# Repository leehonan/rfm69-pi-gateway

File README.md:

# Meterman Gateway (RFM69-to-Pi Gateway)

This repo contains PCB designs and firmware for a 'meter gateway' that communicates with one or more 'meter nodes' over packet radio.  It acts as a radio gateway between these and logic running on a local server.  Hardware consists of a ATMEGA 328P (with RFM69 radio), and a daughterboard to mate to a Raspberry Pi for Serial UART TX/RX and power (AKA a Pi Hat).  The PCB design could be used for a general-purpose RFM69-Pi Gateway, hacking the firmware code as needed.

(Note that as above a proper case is TBC)

This Gateway is part of a basic electricity monitoring system described at http://leehonan.com/meterman.  The 'MeterMan' system consists of:

* One or more [MeterNodes](https://github.com/leehonan/meterman-node), transmitting energy consumption at set intervals using sub-GHz packet radio (RFM69 @ 434/868/915MHz).

* The Gateway, being a Raspberry Pi 'Hat' that bridges the RFM69 network to a Raspberry Pi's UART Serial interface.

* A [Server](https://github.com/leehonan/meterman-server) that runs on the Pi, maintains energy consumption data, and provides access to this and other operational data through an API, a file journal, and a realtime socket API (socket API is TBD).

## This Repo

This (Gateway) repo consists of:

* The Gateway PCB design (authored in KiCad).  This mounts onto a Raspberry Pi, with ~12mm x 2.5mm spacers being recommended.

* 3D shape files (.STL) for the gateway housing (WIP).

* Source code for the Gateway firmware (AVR C with Arduino extensions).  

All contents are licenced according to the MIT licence.

## Gateway Overview
The Gateway is essentially a bridge between nodes on a RFM69 network and a local application connected to the Pi's UART serial port.  As the Gateway has been designed to support MeterNodes, much of the context for it is best understood by consulting the more comprehensive [MeterNode's ReadMe](https://github.com/leehonan/meterman-node/blob/master/readme.md) - it is not repeated here (DRY).

The Gateway itself comprises:
* A DC power sub-circuit, switchable using a jumper between 5V from the Raspberry Pi and FTDI (or off if no FTDI connection).  Uses a MCP1700 regulator to supply 3.3VDC.  

* An ATMega 328P MCU sub-circuit, along the lines of common 'minimal low-power Arduino' circuits.  FTDI Header for programming and control.

* A radio sub-circuit with an RFM69HW module.  The design uses an RP-SMA connector, but the PCB also supports uFL or a wire antenna.

The gateway does not have a 'real' RTC.  A timer-based clock is implemented in firmware, although this relies on regular synchronisation with its NTP-synced Pi (e.g. every 15m) to be accurate.

## Operation

 The Gateway:
* Polls for radio messages from nodes, responding to these as needed.  These may indicate events or status changes, which are passed through to the connected application (such as a meter update event).

* Keeps a register of meter nodes, maintaining state information and notifying the connected application when they appear to go offline.

* Polls for serial messages from the connected application, responding to these as needed.  Some of these will cause a particular instruction to be sent to a MeterNode(s) when they are available (e.g. to change their meter value).

* Sends messages to the connected application, such as a request from the Gateway to sync its clock.

The gateway runs continuously and does not sleep.  Its availability for radio messaging can therefore be depended upon by MeterNodes - hence all communication between MeterNodes and their Gateway is initiated by the MeterNodes.

### Gateway Hardware Interface
The MeterNode PCB has the following switches, buttons, headers, and adjustable components.  These are shown below.

* A group of 3 jumpers that toggle between the Pi and FTDI for TX from the MCU, RX by the MCU, and 5VDC In.  If the jumper is in the FTDI position but FTDI is not connected the device will be off.  Conversely if the switch is in the Pi position but a FTDI adapter is connected, power will be drawn from the Pi (with other FTDI functions working as normal).

* A 'Pi Off' button that shuts the Pi down (using the accompanying pi-gw-reboot script).

* A 'Pi Res' button that reboots the Pi (using the accompanying pi-gw-reboot script).

* A MCU Reset button that reboots the MCU.

* A MCU Aux button that can be programmed as needed (currently blinks LED).

* A jumper to allow the Pi to reboot the MCU (used when programming the MCU, safe to leave closed).

* An FTDI header for use with a USB-FTDI adapter.  This is used to upload firmware and also to interact with the MCU directly over a serial connection (viewing events and using the MeterNode's command protocol to view information and change settings).  Firmware can be uploaded using avrdude directly, or via an IDE (such as platform.io).  The use of the FTDI header is usually unnecessary with a Pi connected as all commands/operations can be performed from the Pi using its GPIO pins (assuming the enclosed scripts are installed).

* A breakout header that is used for setup and diagnosis, typically with a multimeter.  These can also be used for hacking together custom solutions.  The positions are described below and pictured above:

| Position | Description |
| :--- |:---|
| A0 - D8 | Access to unused analogue (A0 - A2) and digital (D3-D8) pins on the MCU. |
| GND | DC Ground. |
| 3V3   | 3.3VDC from regulator.  |
| 5V  | ~5VDC from Pi.  |

### Shutdown and Reboot
The Restart/Reboot and Shutdown buttons are connected to GPIO P23 and P24 (board numbering).  They perform a soft reboot or shutdown, equivalent to a `reboot` or `shutdown -h now`.

The enclosed pishutdown.py script needs to be installed for these to function, and to be set to start at boot.

A service script is enclosed in `/src`.  This can be installed as follows:
```
cp pishutdown.service /lib/systemd/system
chmod 644 /lib/systemd/system/pishutdown.service
systemctl daemon-reload
systemctl enable pishutdown.service
systemctl start pishutdown.service
```

Otherwise simple way to start on boot is to use cron, e.g.:
```
@reboot /usr/local/bin/python3.6 /home/pi/pishutdown.py
```

### Uploading Firmware
Firmware is uploaded using avrdude (alternately through an IDE such as atom/platform.io, the Arduino IDE may work too).  For an FTDI adapter with Id A403JXEV on OSX or Linux the command will be something like:

```
sudo avrdude -c arduino -p atmega328p -P /dev/cu.usbserial-A403JXEV -b 115200 -U flash:w:/home/tmp/firmware.hex
```
In practice for the gateway, it is easiest to upload firmware using scp and then to flash over the GPIO header using avrdude.  E.g.
```
scp /Users/lee/meter_gateway/firmware.hex meterman@meterbox:

sudo avrdude -c arduino -p atmega328p -P /dev/serial0 -b 115200 -U flash:w:/home/meterman/firmware.hex
```

For this to work, avrdude needs to be patched to work around the absence of a DTR pin on the RPi.  The files are enclosed in this repo's `/src` directory, and can be installed using the following commands (as sudo), or by executing the meterman setup script (from the meterman repo) on the pi.
```
cp autoreset /usr/bin
cp avrdude-autoreset /usr/bin
chmod +x /usr/bin/autoreset
chmod +x /usr/bin/avrdude-autoreset
mv /usr/bin/avrdude /usr/bin/avrdude-original
ln -s /usr/bin/avrdude-autoreset /usr/bin/avrdude
```

The flash process will only work if there are no active serial sessions on the port chosen.  Flashing fails occasionally for no clear reason, but will work when retried.

### Serial Communication & Console
A serial connection can be made using a baud of 115200bps, 8N1 (8 data bits, no parity bit, 1 stop bit).  

On the RPi minicom can be used (as can screen etc) to open a terminal:
```
sudo minicom -b 115200 -o -D /dev/serial0
```
Ensure that hardware flow control is off.

The following commands are available through the serial console (case-insensitive):

| Command | Description |
| :--- |:---|
| help | Prints a list of commands. |
| z  | Toggles sleep on and off. |
| dumpg | Prints (dumps) Gateway config and status to the console.  |
| dumpn | Prints (dumps) node status to the console (with dumpn=[node_id] to specify a node).  |
| rcfg | Reset Config.  Resets configuration values stored in EEPROM to defaults and re-applies these.  |
| time | Prints current time from RTC. Set using time=[seconds since UNIX epoch, UTC] |
| logl | Prints log level - ERROR, WARN, INFO, DEBUG.  Set with logl=[log level]|
| ekey | Prints encryption key (16 byte AES) used by network participants for radio comms.  Set with ekey=[encryption key], e.g. ekey=CHANGE_THIS_ASAP|
| neti | Prints Gateway's Network Id comprised of octets akin to an IP address but with an extra subnet (as the 4 octets define a subnet, with node addressing within this).  Set with neti=[network_id].  At least two octets need to be non-zero so 0.0.1.1 is the 'lowest' usable network subnet.  E.g. neti=0.0.1.1|
| gwid | Prints the 'node id' for the gateway.  This should be 1 by convention, but can be any unallocated address from 1 to 253. Set with gwid=[gateway Id]|
| txpw | Print/set transmission power (set with TXPW=[tx power in dBi]).  For RFM69W range is -18 to +13, for RFM69HW is -14 to +20. Higher values will use more power. |
| enta | Sets meter nodes to be in alignment mode (set on with ENTA=1, off with ENTA=0). When on, a change to a MeterNode's RTC will cause it to wait until mm:00 before opening a new entry.  |

### Pi-to-Gateway Serial Message Protocol
The serial port is also used for communication between the Pi and the Gateway.  In normal operation the user-driven command protocol should be unnecessary, as all key functions are exposed through this interface (intended to be used by the Meterman server application).

Messages are distinguished from user commands and user feedback/logging by a prefix:
* for a message from the Gateway to the Pi Server ```G>S:<message>```

* for a message from the Pi Server to the Gateway ```S>G:<message>```

| Message | From | To | Description|
| :--- |:---| :--- |:---|
| Get Time  | gateway | server | Request for server to return time, allowing gateway to sync its internal clock. <br>Format: `GTIME`<br>E.g.: `GTIME` |
| Set Time | server | gateway | Instruction to gateway to set its clock to the time provided (seconds since UNIX epoch) <br>Format: `STIME;<new_epoch_time_utc>`<br>E.g.: `STIME;1502795790`|
| Set Time Ack  | gateway | server | Acknowledges receipt of valid instruction.<br>Format: `STIME_ACK`<br>E.g.: `STIME_ACK` |
| Set Time Nack  | gateway | server | Negative acknowledgement of set time instruction, likely malformed. <br>Format: `STIME_NACK`<br>E.g.: `STIME_NACK` |
| Get Gateway Snapshot | server | gateway | Request for gateway status dump. <br>Format: `GGWSNAP`<br>E.g.: `GGWSNAP` |
| Gateway Snapshot | gateway | server | Dump of Gateway Status <br>Format: `GWSNAP;<gateway_id>,<when_booted>,<free_ram>,<time>,<log_level>,<encrypt_key>,<network_id>,<tx_power>`<br>E.g.: `GWSNAP;1,1496842913428,577,1496842913428,DEBUG,PLEASE_CHANGE_ME,0.0.1.1,13` |
| Get Node Snapshot | server | gateway | Requests a dump of a node's state from the Gateway.  All nodes observed by the gateway since boot will be returned (there is no registration process - any with correct subnet and key are assumed to be valid members). <br>Format: `GNOSNAP;<node_id>   - returns all nodes if no node_id or node_id=254`<br>E.g.: `GNOSNAP;2` |
| Node Snapshot | gateway | server | A snapshot of one or more nodes, delimited by ';'. <br>Format: `NOSNAP;[1..n of [<node_id>,<batt_voltage>,<up_time>,<sleep_time>,<free_ram>,<when_last_seen>,<last_clock_drift>,<meter_interval>,<meter_impulses_per_kwh>,<last_meter_entry_finish>,<last_meter_value>,<puck_led_rate>,<puck_led_time>,<last_rssi_at_gateway>]]`<br>E.g.: `NOSNAP;2,4500,15000,20000,600,1496842913428,500,5,1496842913428,3050,1,100,1000,-70` |
| Get Node Snapshot Nack | gateway | server | Negative acknowledgement of request, likely malformed. <br>Format: `GNOSNAP_NACK;<node_id>`<br>E.g.: `GNOSNAP_NACK;2` |
| Meter Update - with Current | gateway | server | Pass-through of message from meterman node, with envelope. <br>Format: `MUPC;<node_id>,<MUPC radio message>`<br>E.g.: `MUPC;2,MUPC,1496842913428,18829393;15,1,10.2;15,5,10.7;` |
| Meter Update - without Current | gateway | server | Pass-through of message from meterman node, with envelope. <br>Format: `MUP_;<node_id>,<MUP_ radio message>`<br>E.g.: `MUP_;2,MUP_,1496842913428,18829393;15,1;15,5;15,2;16,3;` |
| Meter Rebase | gateway | server | Pass-through of message from meterman node, with envelope. <br>Format: `MREB;<node_id>,<MREB radio message>`<br>E.g.: `MREB;2,MREB,1496842913428,18829393` |
| General Message (Broadcast) | gateway | server | Pass-through of message from meterman node, with envelope. <br>Format: `GMSG;<node_id>,<GMSG radio message>`<br>E.g.: `GMSG;2,GMSG,message` |
| Set Meter Value | server | gateway | Requests a reset of a node's meter value to the watt-hour value specified <br>Format: `SMVAL;<node_id>,<new_meter_value>`<br>E.g.: `SMVAL;2,10` |
| Set Meter Value Ack | gateway | server | Acknowledges receipt of valid instruction. <br>Format: `SMVAL_ACK;<node_id>`<br>E.g.: `SMVAL_ACK;2` |
| Set Meter Value Nack | gateway | server | Negative acknowledgement of request, likely malformed. <br>Format: `SMVAL_NACK;<node_id>`<br>E.g.: `SMVAL_NACK;2` |
| Set Puck LED | server | gateway | Requests a change of a node's puck LED rate and time. <br>Format: `SPLED;<node_id>,<new_puck_led_rate>,<new_puck_led_time>`<br>E.g.: `SPLED;2,1,100` |
| Set Puck LED Ack | gateway | server | Acknowledges receipt of valid instruction. <br>Format: `SPLED_ACK;<node_id>`<br>E.g.: `SPLED_ACK;2` |
| Set Puck LED Nack | gateway | server | Negative acknowledgement of request, likely malformed. <br>Format: `SPLED_NACK;<node_id>`<br>E.g.: `SPLED_NACK;2` |
| Set Meter Interval | server | gateway | Requests a change of a node's metering interval to the value specified.  The interval is the period in seconds at which meter entries are created i.e. (resolution). <br>Format: `SMINT;<node_id>,<new_meter_interval>`<br>E.g.: `SMINT;2,10` |
| Set Meter Interval Ack | gateway | server | Acknowledges receipt of valid instruction. <br>Format: `SMINT_ACK;<node_id>`<br>E.g.: `SMINT_ACK;2` |
| Set Meter Interval Nack | gateway | server | Negative acknowledgement of request, likely malformed. <br>Format: `SMINT_NACK;<node_id>`<br>E.g.: `SMINT_NACK;2` |
| Set GITR | server | gateway | Sends request to gateway to set node's gateway instruction polling rate to more aggressive value for a temporary period <br>Format: `SGITR;<node_id>,<tmp_poll_rate>,<tmp_poll_period>`<br>E.g.: `SGITR;2,30,300` |
| Set GITR Ack | gateway | server | Acknowledges receipt of valid instruction. <br>Format: `SGITR_ACK;<node_id>`<br>E.g.: `SGITR_ACK;2` |
| Set GITR Nack | gateway | server | Negative acknowledgement of request, likely malformed. <br>Format: `SGITR_NACK;<node_id>`<br>E.g.: `SGITR_NACK;2` |
| Node Dark Alert | gateway | server | One-time alert on node going from seen to 'missing' after configured period <br>Format: `NDARK;<node_id>,<last_seen>`<br>E.g.: `NDARK;2,1496842913428` |

### Radio Protocol
See the <a href="https://github.com/leehonan/meterman-node/blob/master/readme.md#radio-protocol">MeterNode Radio Protocol documentation</a>.

## Implementation - Gateway Firmware
For simplicity, the firmware is implemented as a single C++ program (no header file), although it will need supporting libraries to compile.  There is some redundancy versus the companion meternode firmware - the common components may be moved to a library.  Some Arduino library features are used.

The firmware requires a 328P that has been flashed with Optiboot.  It uses about 90% available program flash memory.

Depending on configuration, about 500 bytes RAM will remain free at runtime (on average, of 2K).  

There are a number of configuration settings at the beginning of the source code.  Particular attention should be paid to the 'Main Config Parameters'.

Note that a version is set in the firmware, and broadcast on boot.

The code is fairly well-documented so isn't covered further here.

## Implementation - PCBs & Cases

The Gateway PCB measures 65x56mm, being a standard Raspberry Pi Hat size.

A case for the Pi and Gateway is TBD, currently I use a regular Pi case and tape the antenna to it.

Of course, the MeterNode and Gateway antennae should be in the same orientation to maximise signal strength.

### Gateway Schematic & PCB

The PCB design minimises the use of SMT components, and uses through-hole instead.  It is 'hobbyist-friendly' with the only SMT component being the easily-solderable RFM69 and the slightly fiddly uFL connector.  

Highlights:

* The MCP1700 regulator (3.3V) was chosen for consistency with the MeterNode.

* Unlike the MeterNode, I usually use a uFL connector here.  Of course a RP-SMA connector, or even a wire of the appropriate length can be used instead.

* Any RFM69W or RFM69HW module will work.  I use the RFM69HW here (as opposed to the MeterNode's RFM69W) because it is cheaper and there is no need to minimise power consumption on the gateway.

* Of course, the Pi's 2x20 GPIO header needs to face downward (towards the Pi).  Be mindful of this when assembling.

### Parts List

Approx total is USD$11 (not including labour!).  That assumes you purchase common parts in quantity from Chinese suppliers (e.g. resistors, capacitors).  Otherwise cost will be radically higher.  

| Part | Qty | Approx <br>Item Cost<br>(USD) | Comments |
|:---| :--- |:---|:---|
| PCB | 1 | $0.50 | E.g. 10 for $5 at PCBWay |
| Case | 1 | $0.50 | 3D-printed, PLA |
| LED | 1 | $0.02 | Super-bright 5mm, 20mA |
| RP-SMA 3dbi Antenna | 1 | $2.90 | I use higher quality ones via RocketScream, cheaper options available. |
| uFL Connector w/ pigtail | 1 | $1.00 |  |
| MCP1700 Regulator | 1 | $0.50 | 3.3V, TO-92 |
| MCU - ATMEGA 328P | 1 | $1.80 | DIP-28, with holder |
| 16MHz Crystal | 1 | $0.20 | |
| RFM69HW Module | 1 | $2.50 | SMD |
| Resistor - 1 KOhm | 1 | $0.01 | 0.25W |
| Resistor - 10 KOhm | 6 | $0.01 | 0.25W |
| Capacitor - 22 pF | 2 | $0.01 | Ceramic disc |
| Capacitor - 100 nF | 4 | $0.01 | Monolithic, Ceramic |
| Capacitor - 1 uF | 1 | $0.02 | Electrolytic |
| Capacitor - 1 uF | 2 | $0.01 | Monolithic, Ceramic |
| Capacitor - 10 uF | 1 | $0.02 | Electrolytic, 4x7mm |
| Diode - 1N4148 | 1 | $0.01 |  |
| 6x6mm pushbutton | 4 | $0.02 |  |
| Pin Header | 1 | $0.02 | 6P, 2.54mm pitch |
| Pin Header | 3 | $0.01 | 3P, 2.54mm pitch |
| Pin Header | 1 | $0.01 | 2P, 2.54mm pitch |
| Jumper Cap | 4 | $0.01 | 2P, 2.54mm pitch |
| Pi GPIO Header | 1 | $0.10 | 2x20, 40P, 2.54mm pitch |

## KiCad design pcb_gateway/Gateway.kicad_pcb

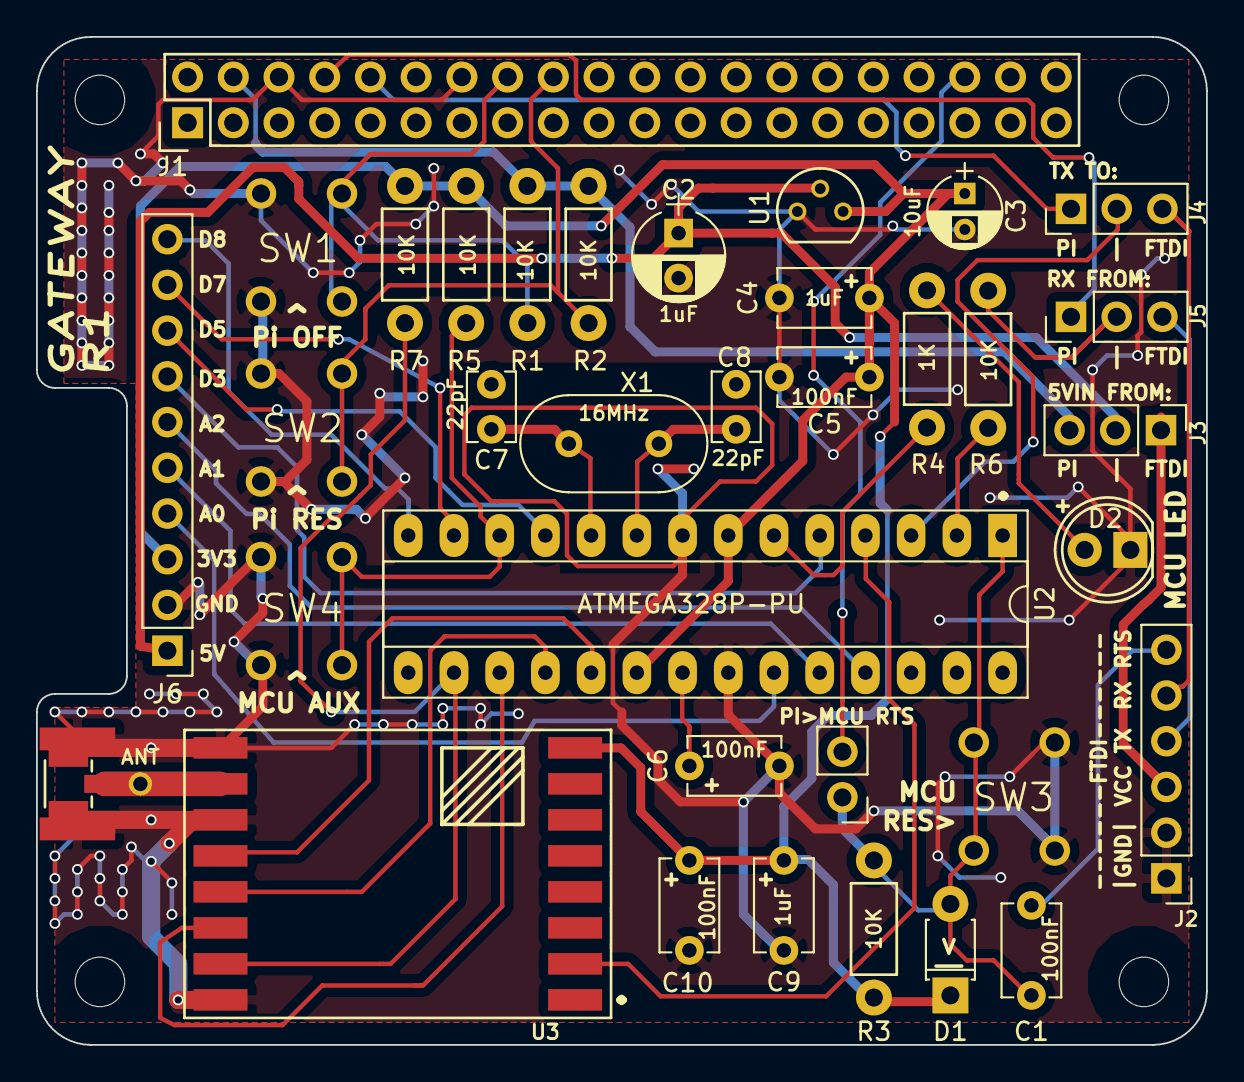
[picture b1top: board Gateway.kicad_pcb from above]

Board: 2 copper layers, 65.0 x 56.0 mm, 37 parts (0 on the bottom side), 36 nets.

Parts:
C1, C5, C6, C10: 100nF; C_Disc_D5.1mm_W3.2mm_P5.00mm
C2: 1uF; CP_Radial_D5.0mm_P2.50mm
C3: 10uF; CP_Radial_D4.0mm_P2.00mm
C4, C9: 1uF; C_Disc_D5.1mm_W3.2mm_P5.00mm
C7, C8: 22pF; C_Disc_D3.8mm_W2.6mm_P2.50mm
D1: 1N4148; D_T-1_P5.08mm_Horizontal
D2: LED; LED-5MM
J1: RPi_GPIO; Pin_Header_Straight_2x20
J2: CONN_FTDI; Pin_Header_Straight_1x06_Pitch2.54mm
J3: JPR_VIN; Pin_Header_Straight_1x03_Pitch2.54mm
J4: JPR_MCU_TX; Pin_Header_Straight_1x03_Pitch2.54mm
J5: JPR_MCU_RX; Pin_Header_Straight_1x03_Pitch2.54mm
J6: CONN_BREAKOUT; Pin_Header_Straight_1x10_Pitch2.54mm
J7: ANT-UFL; U.FL-R-SMT
J8: ANT-SMA; RF-SMA-EDGE
J9: ANT; Pin_Header_Straight_1x01
J10: CONN_01X02; Pin_Header_Straight_1x02_Pitch2.54mm
R1, R2, R3, R5, R6, R7: 10K; Resistor_Horizontal_RM7mm
R4: 1K; Resistor_Horizontal_RM7mm
SW1: PI_BTN_1; 6x6mm_pushbutton
SW2: PI_BTN_2; 6x6mm_pushbutton
SW3: MCU_BTN_RESET; 6x6mm_pushbutton
SW4: MCU_BTN_1; 6x6mm_pushbutton
U1: MCP1700-TO92; TO-92_Molded_Narrow
U2: ATMEGA328P-PU; DIP-28_W7.62mm_Socket_LongPads
U3: RFM69W; RFM69HW_SMD_Handsoldering
X1: 16MHz; Resonator-2pin_w10.0mm_h5.0mm

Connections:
+3V3: C3.1, C4.1, C5.1, C9.2, C10.2, D1.1, J6.3, R3.2, R5.2, R7.2, U1.3, U2.7, U2.20, U3.8
/+5V: C2.1, J3.2, J6.1, U1.2
/ANT: J7.1, J9.1, U3.10
/FTDI_RXD: J2.5, J4.3
/FTDI_TXD: J2.4, J5.3
/MCU_A0: J6.4, U2.23
/MCU_A1: J6.5, U2.24
/MCU_A2: J6.6, U2.25
/MCU_D3: J6.7, U2.5
/MCU_D4: R4.1, U2.6
/MCU_D5: J6.8, U2.11
/MCU_D6: R5.1, SW4.1, U2.12
/MCU_D7: J6.9, U2.13
/MCU_D8: J6.10, U2.14
/MCU_RESET: C1.1, D1.2, J10.1, R3.1, SW3.2, U2.1
/MCU_RX: R6.2, U2.2
/MCU_TX: J4.2, U2.3
/MISO: U2.18, U3.13
/MOSI: U2.17, U3.14
/PI_5V: J1.4, J3.3, R1.2, R2.2
/PI_D23: J1.16, R1.1, SW1.1
/PI_D24: J1.18, R2.1, SW2.1
/PI_RXD: J1.10, J4.1
/PI_TXD: J1.8, J5.1
/RAD_INT: U2.4, U3.2
/RAD_SS: R7.1, U2.16, U3.15
/RTS: C1.2, J2.6
/SCK: U2.19, U3.12
GND: C2.2, C3.2, C4.2, C5.2, C6.2, C7.1, C8.1, C9.1, C10.1, D2.1, J1.6, J1.14, J2.1, J2.2, J6.2, J7.2, J7.3, J8.2, J8.3, J8.4, J8.5, SW1.2, SW2.2, SW3.1, SW4.2, U1.1, U2.8, U2.22, U3.9, U3.11, U3.16
unnamed: C6.1, U2.21
unnamed: C7.2, U2.10, X1.2
unnamed: C8.2, U2.9, X1.1
unnamed: D2.2, R4.2
unnamed: J1.36, J10.2
unnamed: J5.2, R6.1
VCC: J2.3, J3.1

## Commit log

2017-10-16 Create LICENSE
2017-12-04 no message
